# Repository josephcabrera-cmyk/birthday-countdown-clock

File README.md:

# Birthday Countdown Clock

A custom PCB that counts down to a birthday in `days:hours:minutes:seconds` on nine 7-segment displays and plays "Happy Birthday" on a buzzer when it reaches zero.

Final project for ESE 323 at Stony Brook University, Fall 2024, done solo: schematic, layout, assembly, and firmware. The board files are dated November 12, 2024, and the project was submitted December 8, 2024.

[Full demo video](https://youtu.be/9NLcifpYV80)

*The finished board in its printed case: nine displays, the MAX6951 on the left, the DevKit on the right, and the three setup buttons along the bottom edge.*

---

## Overview

Three buttons set the current time and the target date. A DS3231M real-time clock keeps time, the ESP32 works out the time remaining, and the display updates once a second. When the clock reaches the target month, day, hour, and minute, the countdown hits zero and the buzzer plays.

| | |
|---|---|
| **Course** | ESE 323, Stony Brook University, Fall 2024 |
| **MCU** | ESP32-DEVKITC-32E |
| **Real-time clock** | DS3231MZ+TRL (I²C, 400 kHz) |
| **Display driver** | MAX6951CEE+ (SPI, 1 MHz) |
| **Displays** | 9 × SunLED XZFMDK07C, common cathode |
| **Buzzer** | PUI Audio SMTB-0927-TW-R magnetic transducer |
| **Power** | 5 V from Micro-USB through the DevKit, 3.3 V logic |
| **Firmware** | C, ESP-IDF |
| **PCB** | 2 layers, designed in Autodesk EAGLE / Fusion Electronics |

### Pin map

| Function | GPIO | | Function | GPIO |
|---|---|---|---|---|
| I²C SCL | 22 | | Digit 9, segment A | 2 |
| I²C SDA | 21 | | Digit 9, segment B | 4 |
| SPI DIN | 23 | | Digit 9, segment C | 17 |
| SPI CLK | 18 | | Digit 9, segment D | 13 |
| SPI CS | 5 | | Digit 9, segment E | 14 |
| UP button (SW2) | 26 | | Digit 9, segment F | 32 |
| DOWN button (SW3) | 27 | | Digit 9, segment G | 16 |
| SET button (SW1) | 25 | | Digit 9, decimal point | 19 |
| Buzzer | 33 | | | |

---

## Hardware

### Display

The countdown needs nine digits: three for days (up to 365) and two each for hours, minutes, and seconds. The MAX6951 drives eight of them. The ninth, the ones digit of the seconds, is wired straight to eight ESP32 GPIOs through 145 Ω resistors (R8–R15).

The two groups work differently:

- **The eight MAX6951 digits** are multiplexed, and the driver regulates segment current itself, so that side of the board has no per-segment resistors. `RSET` (56 kΩ on ISET) sets the peak segment current for all eight, and `CSET` (27 pF on OSC) sets the multiplex clock together with `RSET`.
- **The ninth digit** is static. Its segments stay on instead of being multiplexed, so it needs its own resistors and draws current the whole time a segment is lit: about 9 mA per segment at 3.3 V with a ~2 V LED drop, or about 72 mA with every segment and the decimal point on. That's more average current than any multiplexed digit, so its brightness doesn't automatically match the other eight.

The decimal point on the ninth digit toggles once a second as a heartbeat, so you can see the main loop is running.

**Why the MAX6951 instead of shift registers:** it handles the multiplexing, per-digit brightness, and decoding itself over SPI. Its decoders are hexadecimal (0–9 and A–F, not BCD) and can be set per digit, and it stores each digit, so one digit can change without rewriting the rest. A chain of 74HC595s would use the same three pins, but the ESP32 would have to handle refresh timing, and every segment of every digit would need its own resistor to keep the brightness even. The MAX6951's segment drivers are also slew-rate limited to reduce EMI.

During setup the driver runs in no-decode mode (`0x00`) so it can spell out `YEAR`, `MONTH`, `DAY`, `HOUR`, `MIN`, `SEC`, and `BIRTHDAY`. During the countdown it switches to hex decode (`0xFF`) so digits can be written as plain numbers.

### Timekeeping

The ESP32's internal oscillator drifts and loses the time on every reset, so a separate RTC keeps time.

The part is the DS3231M, which uses a built-in MEMS resonator instead of the plain DS3231's crystal. It's rated ±5 ppm (±0.432 s/day, or about 2.6 minutes a year) from −45 °C to +85 °C. The plain DS3231 holds ±2 ppm from 0 °C to +40 °C and ±3.5 ppm from −40 °C to +85 °C. The M version is less accurate, but still far better than the ESP32 alone.

There's no backup battery: `VBAT` is tied to ground. That's what the datasheet says to do when there's no backup supply, but it means the RTC loses the time when power is removed, and the clock goes back to setup on every boot. See [Possible improvements](#possible-improvements).

Three RTC pins are unconnected: `32KHZ`, `RST`, and `INT/SQW`. `INT/SQW` is the one that matters. It can output a 1 Hz square wave the firmware could sync to, but since it isn't routed, the firmware polls the RTC instead.

### Power

5 V comes in through the DevKit's Micro-USB connector. The custom board has no connector or regulator of its own. The AMS1117-3.3 on the ESP32-DEVKITC-32E supplies the 3.3 V rail for the MAX6951, the RTC, and the LEDs.

The MAX6951 runs at 3.3 V on purpose. It's rated from 2.7 V to 5.5 V and its logic inputs are referenced to its supply, so at 3.3 V the ESP32's SPI pins drive it directly with no level shifting.

Worst-case current is about 72 mA for the static ninth digit, plus the MAX6951's multiplexed load, plus roughly 80–160 mA for the ESP32. That's within the regulator's rating, but without much headroom, especially inside an enclosure.

`R3` (10 kΩ to 3.3 V) and `C4` (1 µF to ground) delay the ESP32's `EN` pin so it stays in reset until the rail settles. `R4`–`R6` (10 kΩ) are the button pullups.

### Layout

Two things in the board file don't show up in the PDF:

- **Net classes:** `power` and `GND` use 0.35 mm traces, while signal nets use the default, so the supply and return paths are wider than everything else.
- **Test points:** `SCL`, `SDA`, `CLK`, `DIN`, `CS`, the buzzer drive, and both supply rails each have a labeled pad. Every bus can be probed without touching a component pin, which made bring-up much easier.

---

## User interface

Three Omron B3S-1000 switches run the whole interface. Each is active low, with a 10 kΩ pullup and a 1 µF capacitor to ground for a 10 ms RC hardware debounce. The firmware adds a 50 ms software debounce on top.

| Switch | GPIO | Function |
|---|---|---|
| **SW1 (SET)** | 25 | Save the current field and move to the next |
| **SW2 (UP)** | 26 | Increase the current field, wrapping at its limit |
| **SW3 (DOWN)** | 27 | Decrease the current field, wrapping at its limit |

Setup has two stages. First you set the current time (year, month, day, hour, minute, second), which is written to the DS3231. Then a `BIRTHDAY` prompt appears and you set the target month, day, hour, minute, and second. Each field's name is spelled out on the display next to its value, and the limits are enforced as you scroll, including the right number of days in each month and leap years.

Pressing **SET** during the countdown goes back to birthday setup without disturbing the clock.

**Known issue:** going back to birthday setup doesn't fully work. The prompts come back, but the values can't be changed from what was entered at first boot. It's a firmware bug, not a hardware one, since the same buttons set those fields fine the first time. It was found during testing and reported in the course write-up.

**Persistence:** the current time is kept in the DS3231's registers, and the target date only in RAM. Neither survives a power cycle: the RTC has no backup cell, and the target is never written to flash, so both have to be entered again at every boot. The DS3231 can't store the target either. Unlike the DS1307, which has 56 bytes of battery-backed RAM, it has no general-purpose user RAM. Saving the target to the ESP32's NVS would fix this (item 1 below).

---

## Firmware

`firmware/main.c` is a single ESP-IDF application. `app_main()` sets up the buzzer's LEDC channel, I²C, SPI, the MAX6951, the GPIO-driven digit, and the buttons; runs the two-stage setup; then loops about once a second using `vTaskDelay(pdMS_TO_TICKS(1000))`.

Each pass reads all seven time registers from the DS3231 in one I²C transaction, converts them from BCD, and works out the days remaining with `mktime()` and `difftime()` against a `struct tm` for the target, rolling over to next year once the date has passed. Then it writes eight digits over SPI and the ninth over GPIO.

The buzzer is triggered from the same loop, not by an RTC alarm. When the month, day, hour, and minute match the target and the seconds are zero, `play_birthday_song()` runs, and a latch stops it from retriggering. An RTC alarm wouldn't have worked anyway: the DS3231's alarms can match the day of the month but not the month, so the alarm would go off every month.

The notes come from LEDC hardware PWM at 10-bit resolution and 50% duty, with the frequency changed for each note.

### Building

```bash
idf.py set-target esp32
idf.py build
idf.py -p COM3 flash monitor
```

Use your board's port in place of `COM3` (usually `/dev/ttyUSB0` on Linux or macOS). `main.c` goes in the `main/` folder of an ESP-IDF project with a matching `CMakeLists.txt`.

### Modularized version

`firmware/modularized-code/` is the same firmware split by peripheral (`max6951`, `ds3231`, `direct_led`, `display`, `buttons`, `buzzer`, `setup_ui`, and `countdown`, each with a header), set up as a complete ESP-IDF project.

It's a readability refactor only. Behavior is unchanged, and the known issues above are still there. `firmware/main.c` is the version that was built and demoed. Read the [notes in that folder](firmware/modularized-code/README.md) before using it.

---

## Repository structure

```
.
├── firmware/
│   ├── main.c                    # Application firmware, as built (ESP-IDF)
│   └── modularized-code/         # Same firmware split by peripheral
│       ├── CMakeLists.txt
│       └── main/                 # max6951, ds3231, direct_led, display,
│                                 #   buttons, buzzer, setup_ui, countdown
├── hardware/
│   ├── schematic.pdf             # Schematic
│   ├── board-layout.pdf          # PCB layout
│   ├── bill-of-materials.pdf     # BOM
│   ├── board-3d.step             # 3D model of the assembled board
│   └── source/
│       ├── birthday-countdown-clock.sch  # EAGLE 9.7 schematic
│       ├── birthday-countdown-clock.brd  # EAGLE 9.7 board
│       └── bill-of-materials.xlsx        # BOM source
└── docs/
    ├── demo.gif
    ├── board-assembled.jpg       # Finished board in its printed case
    ├── board-assembly.jpg        # Partway through hand assembly
    ├── final-paper.pdf           # ESE 323 course write-up, Dec 2024
    ├── presentation.pdf          # ESE 323 project presentation
    └── source/
        ├── final-paper.docx      # Editable original
        └── presentation.pptx     # Editable original
```

The PDFs are for reading. The editable originals in `hardware/source/` open in Autodesk EAGLE 9.7 or later and in Fusion Electronics. The schematic and board share a file name, which is how EAGLE pairs them.

[`docs/final-paper.pdf`](docs/final-paper.pdf) and [`docs/presentation.pdf`](docs/presentation.pdf) are the original December 2024 course submissions, including the enclosure design and the test results that document the re-entry bug. The paper is as submitted, minus a closing section of feedback for the instructor. The Word and PowerPoint originals are in `docs/source/`.

`board-3d.step` is the assembled board as a solid model (AP214 schema), so it can be measured and used to design an enclosure around it. It opens in FreeCAD, KiCad, Onshape, SolidWorks, and Inventor.

---

## Manufacturing

JLCPCB made the bare 2-layer boards. The parts came from DigiKey, and everything was soldered by hand.

The parts were chosen to make that practical: every passive is 0805, the RTC is an 8-pin SOIC, and the display driver is a 16-pin QSOP. There's no BGA or fine-pitch QFN, and the DevKit sits on a through-hole footprint. The QSOP's 0.635 mm pitch is the hardest thing to solder.

*Partway through assembly. The MAX6951, the RTC passives, and the `RSET`/`CSET` network are on; the displays, switches, and buzzer aren't yet. The labeled test points and the R8–R15 resistors next to LED8 are visible on the silkscreen.*

---

## Possible improvements

Some of these were noted in the December 2024 write-up. The rest came from going back through the board file and the datasheets later.

### Firmware

1. **Save the target date in NVS.** It's in RAM now and lost at every power cycle. `nvs_set_u8` for month and day, `nvs_commit`, and a first-boot check would fix the most annoying part of using the clock. Flash wear isn't a concern, since it's only written a handful of times.

2. **Fix birthday re-entry.** Pressing `SET` during the countdown brings back the birthday prompts, but the values can't be changed. This was known at submission and is the most visible firmware bug.

3. **Check the oscillator stop flag at boot.** Bit 7 of register `0Fh` (`OSF`) is set whenever the oscillator has stopped, which means the stored time can't be trusted. The firmware should read it and force time setup instead of counting down from a bad time.

4. **Use the target minute and second in the countdown.** Setup collects a target hour, minute, and second, but the countdown math assumes the minute is zero. The buzzer check does compare the minute, so the song plays at the right time, but the time remaining on the display is off for any target that isn't on the hour.

5. **Play the melody near the buzzer's resonance.** The transducer's 95 dBA rating is at its 2.7 kHz resonant frequency, but the melody's notes run from 262 Hz to 494 Hz, about 2.5 to 3.4 octaves below that, so it's much quieter than it could be. Transposing the melody up, or using a single 2.7 kHz tone, would be much louder at no extra cost.

### Hardware

6. **Keep the time through power loss.** With `VBAT` at ground, the RTC loses the time whenever power drops, which throws away its main advantage over the ESP32's internal timer. A coin cell fixes that. The other option, noted at the time, is to drop the RTC and get the time over Wi-Fi, which the ESP32 already has. That's cheaper, much more accurate than ±5 ppm, and gets rid of setting the time at every boot, but the clock would need a network to be correct.

7. **Route `INT/SQW` to a GPIO** and update the display from the DS3231M's 1 Hz square wave instead of `vTaskDelay`. Polling works, but the display updates slowly drift relative to the RTC's seconds. `INT/SQW` is open-drain and needs a pullup, and `INTCN` in register `0Eh` powers up as 1 (alarm interrupt mode), so it has to be cleared before the pin outputs the square wave. The DS3231M has no `RS2:RS1` rate-select bits (bits 4:3 of `0Eh` are unused), and its square wave is fixed at 1 Hz, so clearing `INTCN` is the only write needed. The interrupt handler should only notify a task, since I²C should never run from an interrupt.

8. **Drive the buzzer through a transistor.** The SMTB-0927-TW-R has a 16 Ω coil and an 80 mA maximum. With the 47 Ω series resistor, an ideal 3.3 V source would push about 52 mA. That's more than the roughly 40 mA an ESP32 GPIO is characterized to source at maximum drive strength while holding VOH ≥ 2.64 V. The 40 mA is a typical figure, not an absolute maximum. In practice the pin's output resistance limits the current and VOH sags, so the GPIO runs past its characterized drive. PWM at 50% duty halves the average current but not the peak. A small N-channel MOSFET or a 2N3904 would fix it.

9. **Move segment A off IO2.** IO2 is an ESP32 boot strapping pin. The LED to the common cathode is a weak enough pull-down that the board boots fine, but there's no reason to tie display state to boot behavior. IO5 (SPI CS) is also a strapping pin, but it idles high and is much less likely to cause trouble.

10. **Add a ground pour and cut the via count.** Ground is routed as traces with no copper pour. The 0.35 mm `GND` net class helps, but a ground plane on the bottom layer would lower impedance and shorten return paths, and nothing on this board switches fast enough to make that hard. The autorouter also left about 86 vias, some close enough to pads to make hand soldering awkward and risk shorts. Routing the power and display nets by hand first, then autorouting the rest, would fix both.

11. **Use USB-C instead of Micro-USB.** That means putting a connector and a regulator on the board instead of using the DevKit's.

12. **Add the enclosure CAD.** A two-part case was designed and 3D printed for this board, with four screw bosses and cutouts for the displays, buttons, buzzer, and Micro-USB connector. The board is in it in the photo above. The design only exists as renders in [`docs/presentation.pdf`](docs/presentation.pdf). The CAD files are missing, so the enclosure is the one part of the project that can't be rebuilt from this repo.

---

## License

- **Firmware** (`firmware/`): MIT. See [LICENSE](LICENSE).
- **Hardware** (`hardware/`): CERN Open Hardware Licence Version 2 – Permissive (`CERN-OHL-P-2.0`). See [hardware/LICENSE](hardware/LICENSE).

MIT is written for software and doesn't map cleanly onto schematics, board files, or mechanical models. CERN-OHL-P is the hardware equivalent at the same permissive level, so both halves of the project have the same practical terms.

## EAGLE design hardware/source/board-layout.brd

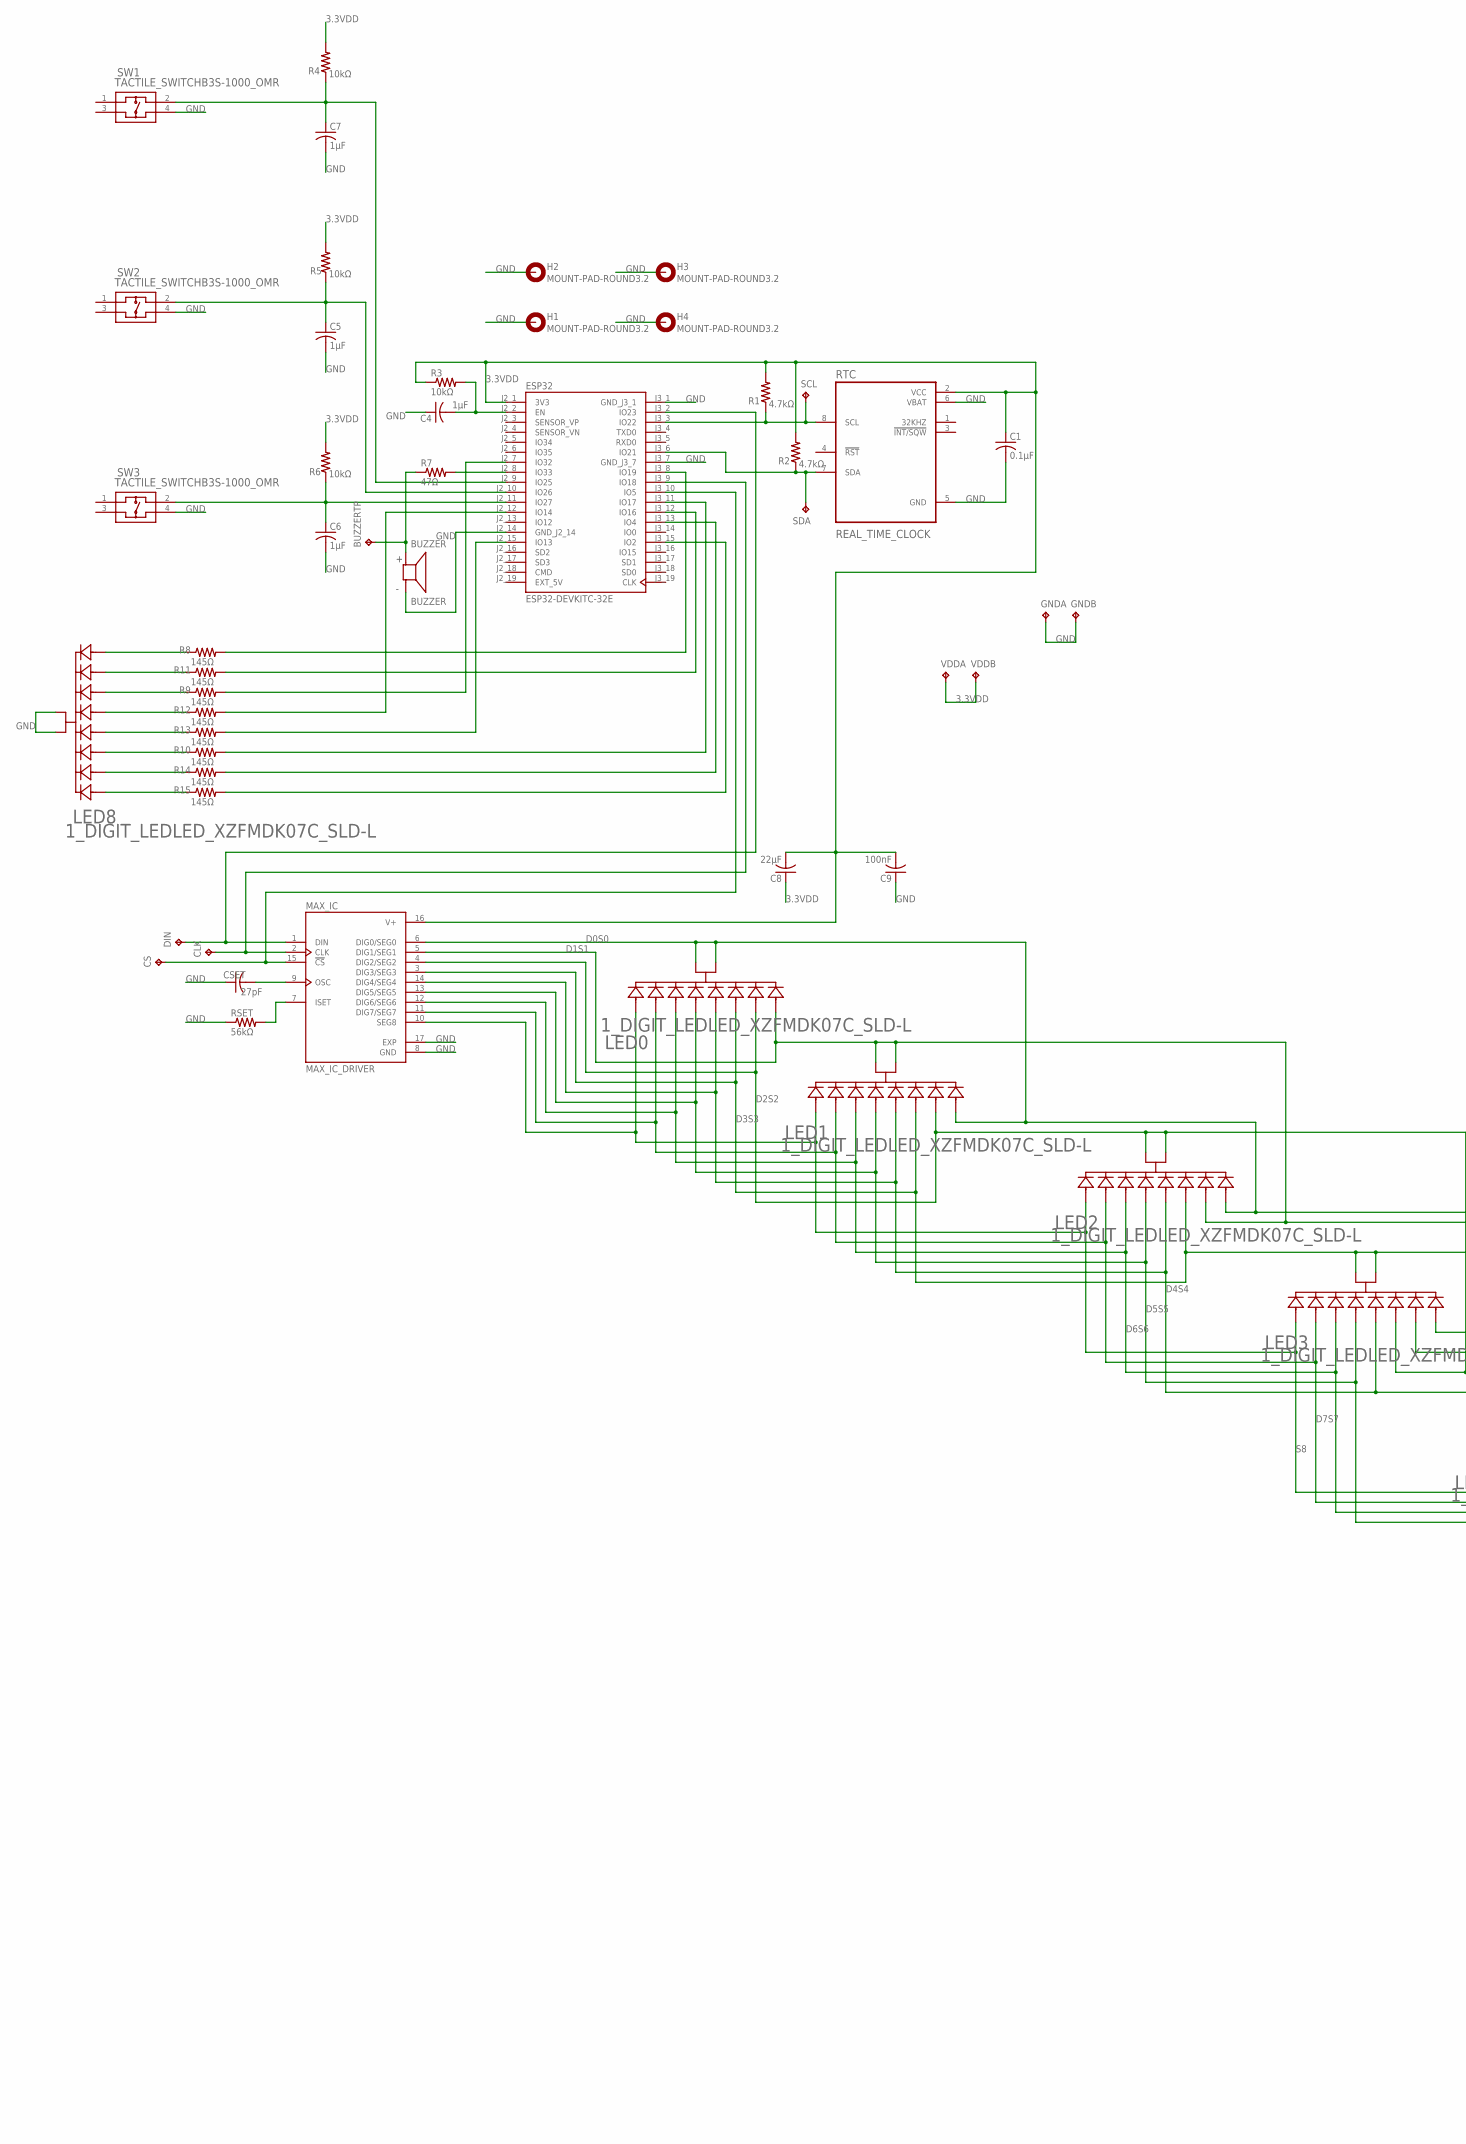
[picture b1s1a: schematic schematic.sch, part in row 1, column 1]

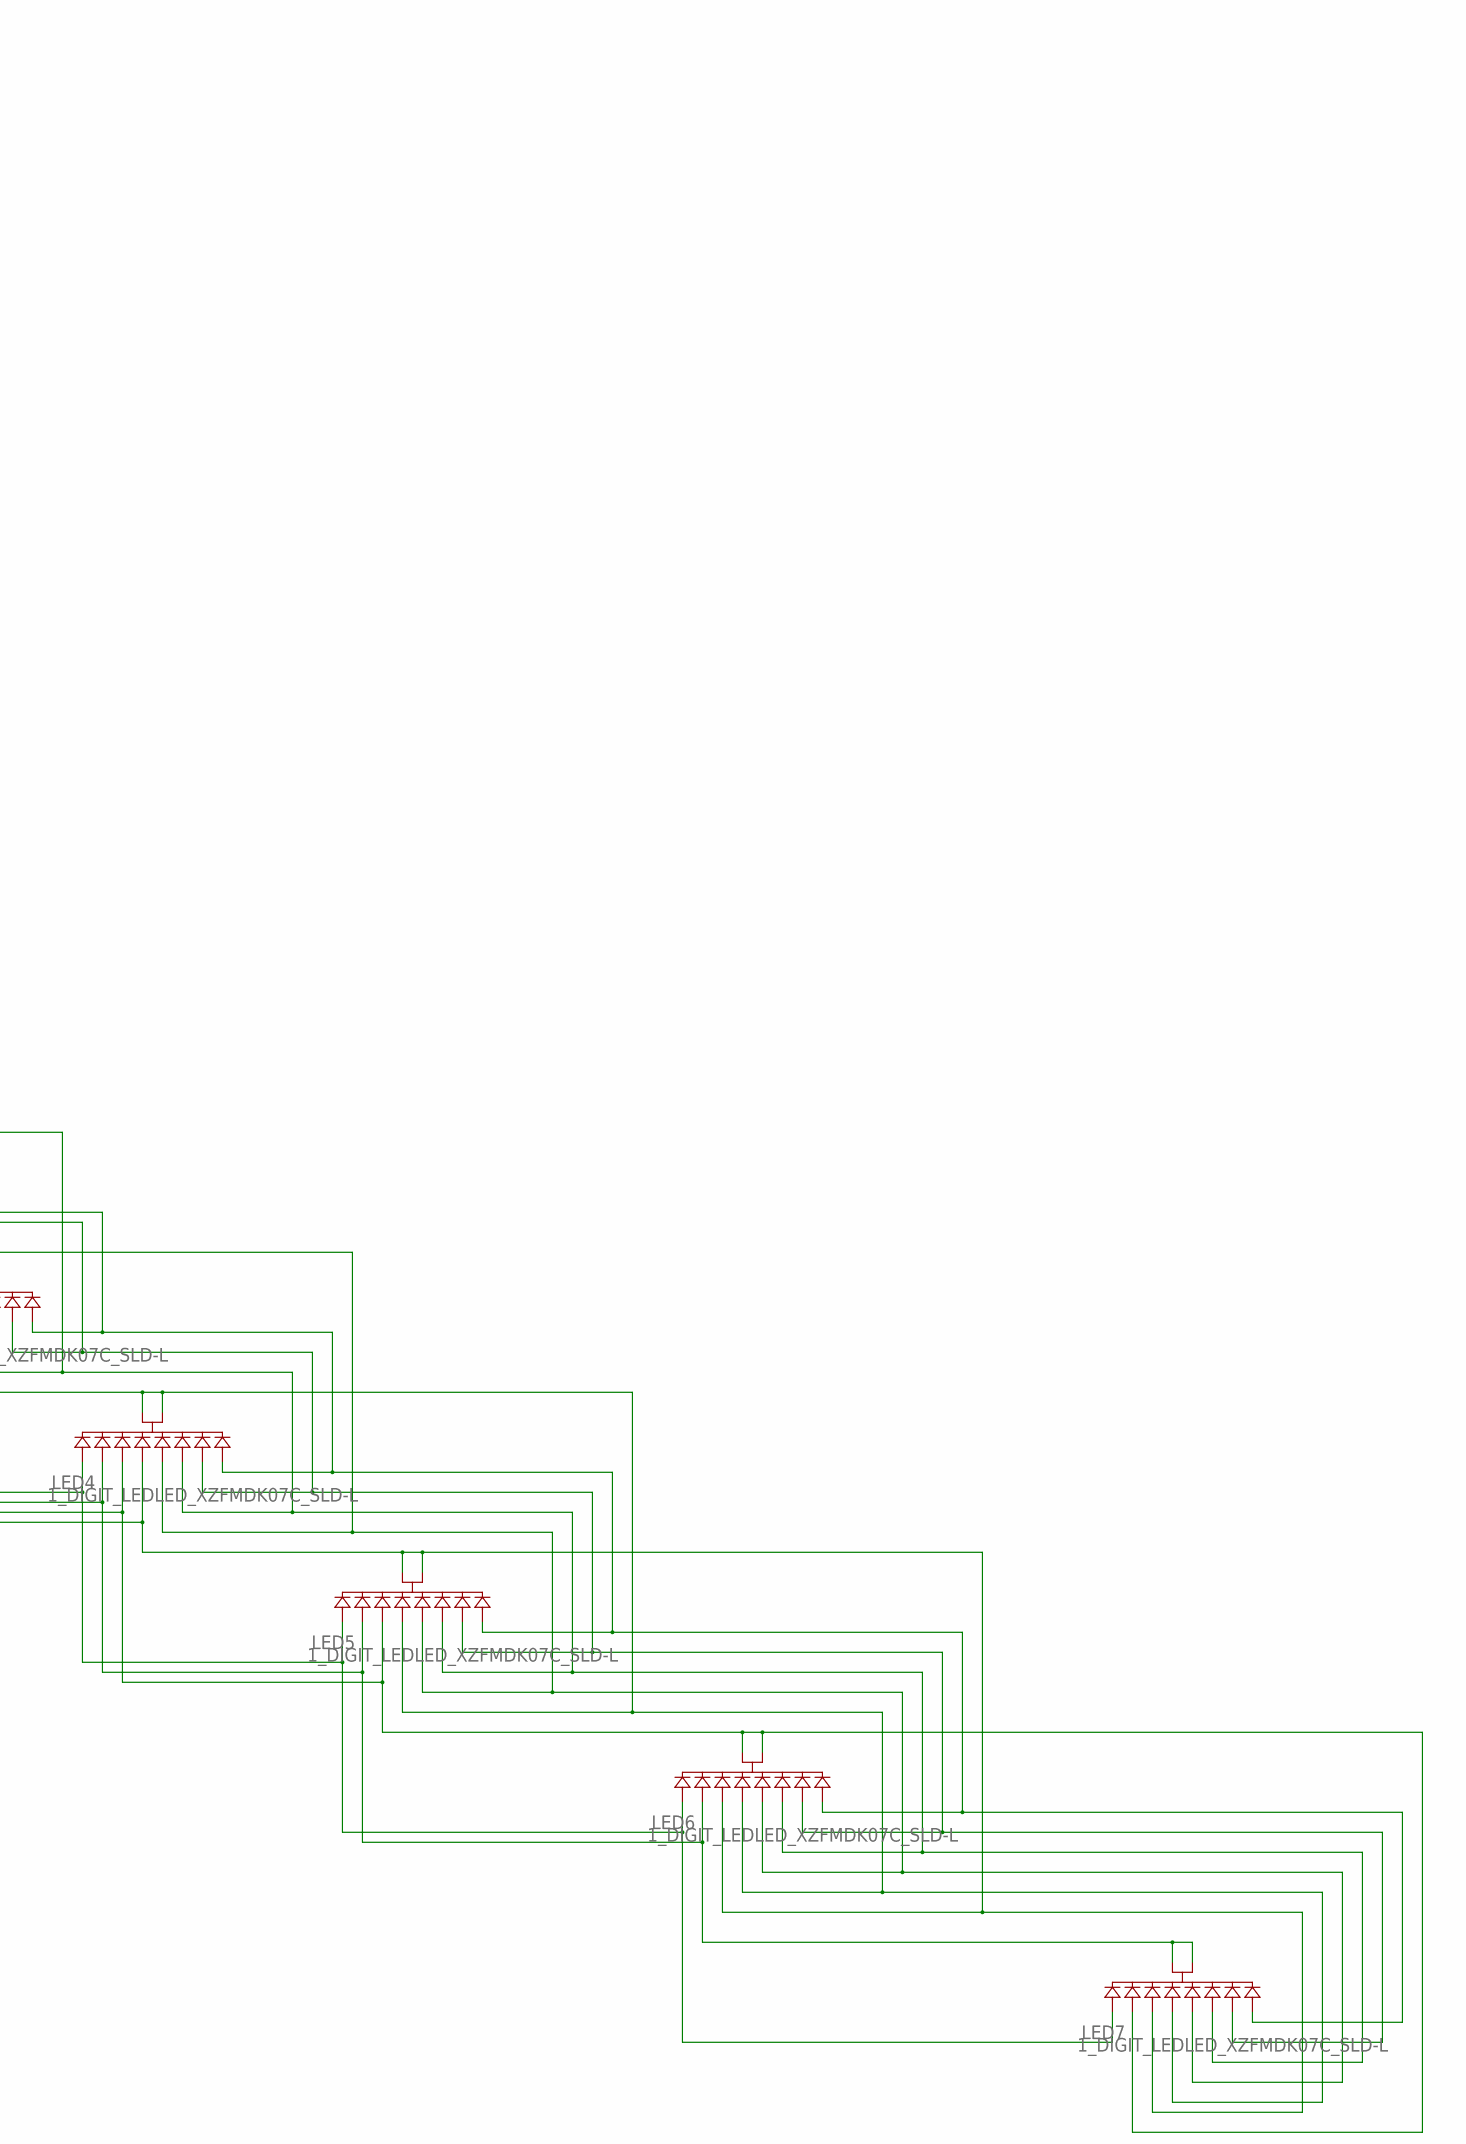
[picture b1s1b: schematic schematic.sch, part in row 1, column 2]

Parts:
BUZZER: BUZZER; XDCR_SMTB-0927-TW-R
BUZZERTP: TPTP20SQ; TP20SQ
C1: 0.1µF; C0805
C4, C5, C6, C7: 1µF; C0805
C8: 22µF; C0805
C9: 100nF; C0805
CLK: TPTP20SQ; TP20SQ
CS: TPTP20SQ; TP20SQ
CSET: 27pF; C0805
DIN: TPTP20SQ; TP20SQ
ESP32: ESP32-DEVKITC-32E; MODULE_ESP32-DEVKITC-32E
GND: TP2P2-38-20; P2-38-20
H1, H2, H3, H4: MOUNT-PAD-ROUND3.2; 3,2-PAD
LED0, LED1, LED2, LED3, LED4, LED5, LED6, LED7, LED8: 1_DIGIT_LEDLED_XZFMDK07C_SLD-L; LED_XZFMDK07C_SLD-L
MAX_IC: MAX_IC_DRIVER; SOP63P602X173-17N
R1, R2: 4.7kΩ; R0805
R3, R4, R5, R6: 10kΩ; R0805
R7: 47Ω; R0805
R8, R9, R10, R11, R12, R13, R14, R15: 145Ω; R0805
RSET: 56kΩ; R0805
RTC: REAL_TIME_CLOCK; SOIC127P600X175-8N
SCL: TPTP20SQ; TP20SQ
SDA: TPTP20SQ; TP20SQ
SW1, SW2, SW3: TACTILE_SWITCHB3S-1000_OMR; B3S-1000_OMR
VDD: TP2P2-38-20; P2-38-20

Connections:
3.3VDD: C1.1, C8.1, C8.2, C9.2, ESP32.J2_1 (3V3), MAX_IC.16 (V+), R1.2, R2.2, R3.1, R4.2, R5.2, R6.2, RTC.2 (VCC), VDD.TP-1, VDD.TP-2
D0S0: LED0.3, LED0.8, LED1.5, LED2.5, LED3.5, LED4.5, LED5.5, LED6.5, LED7.5, MAX_IC.6 (DIG0/SEG0)
D1S1: LED0.5, LED1.3, LED1.8, LED2.10, LED3.10, LED4.10, LED5.10, LED6.10, LED7.10, MAX_IC.5 (DIG1/SEG1)
D2S2: LED0.10, LED1.10, LED2.3, LED2.8, LED3.9, LED4.9, LED5.9, LED6.9, LED7.9, MAX_IC.4 (DIG2/SEG2)
D3S3: LED0.9, LED1.9, LED2.9, LED3.3, LED3.8, LED4.1, LED5.1, LED6.1, LED7.1, MAX_IC.3 (DIG3/SEG3)
D4S4: LED0.1, LED1.1, LED2.1, LED3.1, LED4.3, LED4.8, LED5.2, LED6.2, LED7.2, MAX_IC.14 (DIG4/SEG4)
D5S5: LED0.2, LED1.2, LED2.2, LED3.2, LED4.2, LED5.3, LED5.8, LED6.4, LED7.4, MAX_IC.13 (DIG5/SEG5)
D6S6: LED0.4, LED1.4, LED2.4, LED3.4, LED4.4, LED5.4, LED6.3, LED6.8, LED7.6, MAX_IC.12 (DIG6/SEG6)
D7S7: LED0.6, LED1.6, LED2.6, LED3.6, LED4.6, LED5.6, LED6.6, LED7.3, LED7.8, MAX_IC.11 (DIG7/SEG7)
EXT_5V: ESP32.J2_19 (EXT_5V)
GND: BUZZER.N (-), C1.2, C4.1, C5.2, C6.2, C7.2, C9.1, CSET.1, ESP32.J2_14 (GND_J2_14), ESP32.J3_1 (GND_J3_1), ESP32.J3_7 (GND_J3_7), GND.TP-1, GND.TP-2, H1.B3,2, H2.B3,2, H3.B3,2, H4.B3,2, LED8.3, LED8.8, MAX_IC.8 (GND), MAX_IC.17 (EXP), RSET.1, RTC.5 (GND), RTC.6 (VBAT), SW1.4, SW2.4, SW3.4
unnamed: ESP32.J3_6 (IO21), R2.1, RTC.7 (SDA), SDA.TP
unnamed: ESP32.J3_3 (IO22), R1.1, RTC.8 (SCL), SCL.TP
unnamed: MAX_IC.7 (ISET), RSET.2
unnamed: CLK.TP, ESP32.J3_9 (IO18), MAX_IC.2 (CLK)
unnamed: CS.TP, ESP32.J3_10 (IO5), MAX_IC.15 (!CS)
unnamed: CSET.2, MAX_IC.9 (OSC)
unnamed: C4.2, ESP32.J2_2 (EN), R3.2
unnamed: LED8.5, R8.1
unnamed: ESP32.J3_15 (IO2), R15.2
unnamed: BUZZER.P (+), BUZZERTP.TP, R7.1
unnamed: DIN.TP, ESP32.J3_2 (IO23), MAX_IC.1 (DIN)
unnamed: ESP32.J2_8 (IO33), R7.2
unnamed: ESP32.J3_13 (IO4), R14.2
unnamed: ESP32.J3_11 (IO17), R10.2
unnamed: ESP32.J2_15 (IO13), R13.2
unnamed: ESP32.J2_12 (IO14), R12.2
unnamed: ESP32.J2_7 (IO32), R9.2
unnamed: ESP32.J3_12 (IO16), R11.2
unnamed: ESP32.J3_8 (IO19), R8.2
unnamed: LED8.10, R11.1
unnamed: LED8.9, R9.1
unnamed: LED8.1, R12.1
unnamed: LED8.2, R13.1
unnamed: LED8.4, R10.1
unnamed: LED8.6, R14.1
unnamed: LED8.7, R15.1
unnamed: C5.1, ESP32.J2_10 (IO26), R5.1, SW2.2
unnamed: C6.1, ESP32.J2_11 (IO27), R6.1, SW3.2
unnamed: C7.1, ESP32.J2_9 (IO25), R4.1, SW1.2
S8: LED0.7, LED1.7, LED2.7, LED3.7, LED4.7, LED5.7, LED6.7, LED7.7, MAX_IC.10 (SEG8)

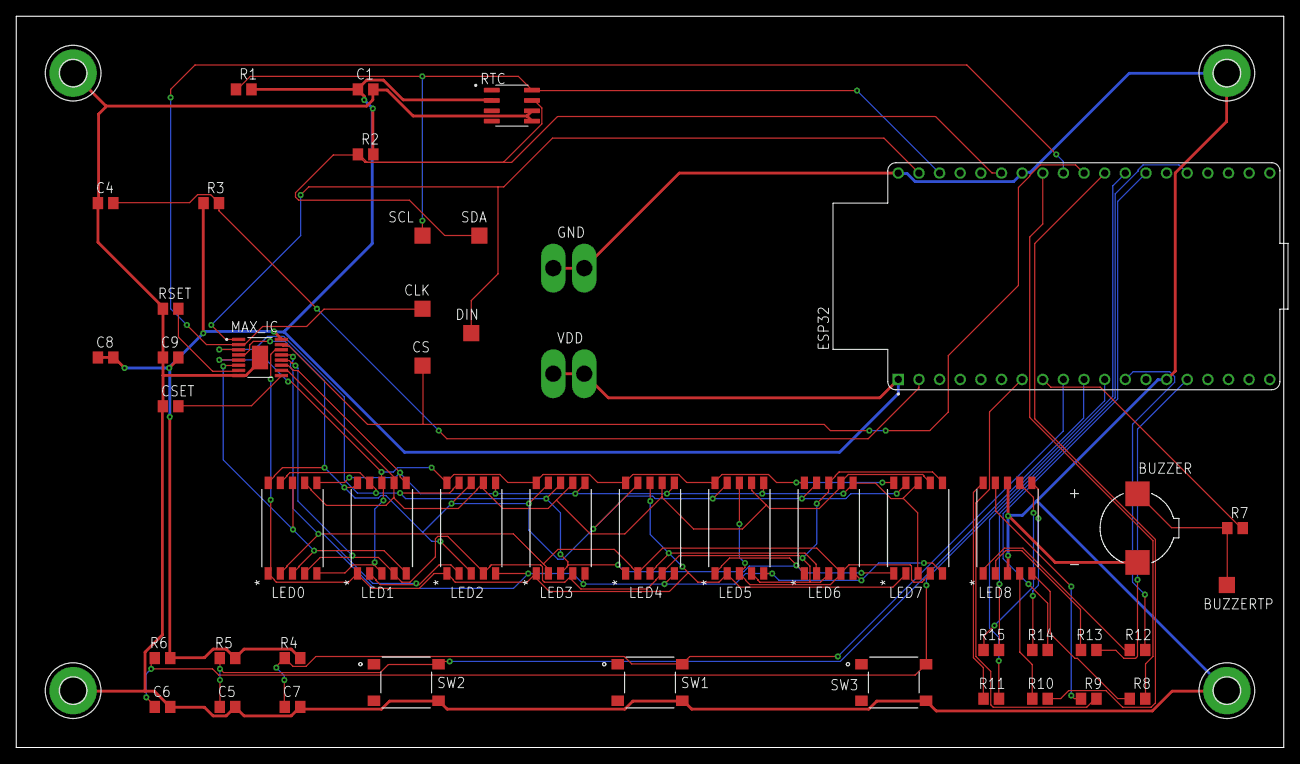
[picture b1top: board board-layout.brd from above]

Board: 2 copper layers, 156.0 x 90.0 mm, 52 parts (0 on the bottom side), 40 nets.

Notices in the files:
parts and their libraries:
COPYRIGHT: Copyright (C) 2024 Ultra Librarian. All rights reserved.
